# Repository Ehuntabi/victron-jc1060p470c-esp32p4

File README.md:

# Joint SPL 145 Control — VictronSolarDisplay port for Guition JC1060P470C_I (ESP32-P4)

**[Español](#español) | [English](#english)**

> La versión no se escribe aquí a mano (se queda vieja): se ve en el equipo en
> Ajustes → Acerca de, o con `git describe --tags --match "v*.*"`.

---

## Índice de documentación / Documentation index

| Si quieres... / If you want to... | Lee / Read |
|---|---|
| Instalar el firmware sin usar terminal / Install without a terminal | [`docs/INSTALACION.md`](docs/INSTALACION.md) |
| Desarrollar: mapa del código, comandos, hardware / Develop: code map, commands, hardware | [`CLAUDE.md`](CLAUDE.md) |
| Flujo multi-PC (sobremesa ↔ portátil) / Multi-PC dev workflow | [`docs/DESARROLLO.md`](docs/DESARROLLO.md) |
| Referencia de hardware: pinouts, esquemáticos, protocolo NE185 / Hardware reference | [`docs/`](docs/) |
| Historial de cambios por versión / Version changelog | [Releases de GitHub](https://github.com/Ehuntabi/victron-jc1060p470c-esp32p4/releases) |
| Guía operativa para la autocaravana (uso interno, portátil) / Motorhome operations guide (internal) | [`AUTOCARAVANA-SETUP.md`](AUTOCARAVANA-SETUP.md) |

---

## Capturas / Screenshots

<table>
  <tr>
    <td align="center"><br><sub>Vista general / Overview</sub></td>
    <td align="center"><br><sub>Batería / Battery</sub></td>
    <td align="center"><br><sub>Solar</sub></td>
  </tr>
  <tr>
    <td align="center"><br><sub>DC/DC</sub></td>
    <td align="center"><br><sub>Inversor / Inverter</sub></td>
    <td align="center"><br><sub>Monitor de batería / Battery monitor</sub></td>
  </tr>
  <tr>
    <td align="center"><br><sub>Frigo / Fridge</sub></td>
    <td align="center"><br><sub>Autocaravana / Motorhome</sub></td>
    <td align="center"><br><sub>Ajustes / Settings</sub></td>
  </tr>
</table>

---

## Español

Port del proyecto [victronsolardisplayesp (multi-device)](https://github.com/CamdenSutherland/victronsolardisplayesp/tree/multi-device) de CamdenSutherland, que a su vez es un fork de [VictronSolarDisplayEsp](https://github.com/wytr/VictronSolarDisplayEsp) de wytr.

Port realizado por **[Ehuntabi](https://github.com/Ehuntabi)**.

### Hardware

| Componente | Detalle |
|---|---|
| **Pantalla** | Guition JC1060P470C_I (7", 1024x600, DSI, touch GT911) |
| **SoC principal** | ESP32-P4 (RISC-V dual core 400 MHz, 32 MB PSRAM, 16 MB Flash) |
| **SoC WiFi/BT** | ESP32-C6 (SDIO vía esp_hosted: CLK=18, CMD=19, D0..D3=14..17) |
| **RTC** | RX8025T (I²C 0x32, SDA=7 / SCL=8 compartido con GT911 y ES8311) + pila CR1220 |
| **microSD** | **SDMMC** (slot 0 IOMUX: CLK=43, CMD=44, D0..D3=39..42; LDO interno canal 4 a 3,3 V), ver `components/datalogger/datalogger.c:241` |
| **Sensores temperatura** | DS18B20 1-Wire en **GPIO 4** (JP1 pin 13, pullup 4.7 kΩ) |
| **Ventilador frigo** | PWM LEDC en **GPIO 5** (JP1 pin 15), 18 kHz. El pin 15 ataca, a través de un optoacoplador **PC817**, un MOSFET **IRLR7843** con resistencia en serie en puerta, resistencia de pull-down y diodo **1N4148** de rueda libre |
| **Audio** | Codec ES8311 + amplificador NS4150 (PA_CTRL=11, I²S MCLK=13/BCLK=12/LRCK=10/DOUT=9) |
| **Cámara** | OmniVision **OV02C10** (MIPI-CSI 2 lanes, RAW10 1928x1092, ~37 fps, JPEG por HW). Comparte el I²C (SDA=7 / SCL=8); sin pines reset/pwdn dedicados |
| **NE185 (autocaravana)** | RS-485 con el cuadro Nordelettronica NE185 vía MAX485 (U8), **UART1 TX=GPIO 26 / RX=GPIO 27**, 38400 8N1, conector J4 (DE/RE automático) |
| **GPS** | u-blox **NEO-M9N** por **UART2 RX=GPIO 3 / TX=GPIO 2** (conector JP1), 38400 8N1. Solo se escucha NMEA; pone el reloj en hora solo |

> Pinout detallado con diagrama del JP1 (pines color-coded) y del CN2 en [`docs/pinout_guition_jc1060p470c_i.pdf`](docs/pinout_guition_jc1060p470c_i.pdf).

### Funcionalidades

#### UI estilo Venus OS
- Cards oscuras con borde de color por rol (cyan/verde/naranja/rojo/púrpura), métricas con número grande + unidad pequeña, pills de estado, gauges circulares para SOC y sombras suaves.
- **Iconos PNG propios** en headers de cards (batería de coche, panel solar, conversor DC/DC, casa) generados como `lv_img_dsc_t` embebidos en flash.
- Helpers reutilizables (`main/ui/ui_card.h`): `ui_card_create`, `ui_card_set_title_img`, `ui_metric_create_compact/_large`, `ui_pill_create`, `ui_arc_soc_create`, `ui_card_pulse`, paleta semántica `UI_COLOR_*`.
- **Pulso de actividad** en la card al recibir un BLE record (sombra anima 50→100→50 % en 600 ms, sin acumular animaciones).
- Pestañas Live/Settings ocultas — navegación con icono ⚙/🏠 discreto en la barra inferior + swipe horizontal del tabview. El botón Home **cierra la subpágina** y deja Settings en su menú principal.
- **Auto-vuelta a Live** tras 60 s sin actividad táctil.

#### Pantalla de bienvenida (splash)
- Logo de la furgo recortado con IA (rembg/u2net) y embebido a 720x400 RGB565 en flash.
- Animación de barra de progreso mientras dura la inicialización (BLE, audio, SD, BT).
- Configurable en Settings → Display: **Logo furgo** (default) o **Sin splash**.

#### Vistas Live
- **Overview** (default): fila horizontal Solar — Bat — Cargas con arc SOC central; debajo TTG + “PV X.X kWh · Cargas Y.Y kWh” acumulados del día.
- **Battery Monitor**: card naranja con arc SOC grande, V/A/W + pill enriquecido (“Cargando 5.5 A” / “Descargando 3.2 A”), barra bipolar de corriente ±50 A, sparkline de potencia (90 puntos), TTG / Consumido / Aux. Tap abre el histórico.
- **Solar Charger**: 2 cards (Solar verde + Salida batería naranja) con pill de estado (Bulk/Absorción/Float).
- **Default Battery**: 3 cards en fila (DC/DC cyan, Batería naranja con arc + sparkline + bar bipolar, Solar verde). En la card DC/DC el rótulo cambia entre `⚡ Alternador` (verde) o `🔋 Bat. motor` (gris) según la tensión.
- **Simple devices** (Inverter, Smart Lithium, AC Charger, etc.): card único con métricas apiladas; color e icono según tipo.
- **Pill rojo “FALLO: X”** en la card cuando un dispositivo Victron reporta `alarm_reason` (BMV/Inverter) o `charger_error` (Solar/DCDC/Orion).

#### Settings
Páginas con cards de borde de color, dropdown scrollable cuando hay overflow, separadores entre sub-bloques:
- **Historial en gráficos** (púrpura): chart 24 h de batería y de temperaturas frigo. Swipe izquierda/derecha **navega por fecha** en los logs guardados en SD (header muestra la fecha seleccionada).
- **Wi-Fi** (naranja): SSID, contraseña y switch on/off que se aplica **en caliente**, sin reiniciar la placa. (Cambiar SSID o contraseña sí necesita apagar y encender el switch para que entre.) Ojo: con el AP apagado, la pantalla de la cabina se queda sin telemetría.
- **Pantalla** (cyan): card combinada **Brillo pantalla + Salvapantallas**; card **Modo nocturno** en una línea (switch + Inicio/Fin + brillo nocturno, brillo aplicado automáticamente entre las horas configuradas según RTC); **Pantalla de bienvenida** (logo furgo o sin splash).
- **Tarjeta SD** (azul): carrusel de capturas y visor de imágenes de la SD.
- **Sonido y alertas** (rojo): volumen, switch silenciar avisos, umbrales SoC y temperatura del frigorífico.
- **Autocaravana** (rosa): agrupa lo propio del vehículo — **Opciones Frigo** (sensores DS18B20, control PWM del ventilador según T_Aletas, umbrales y aprovechamiento de excedente solar), **Victron Keys** (MAC + clave AES por dispositivo, hasta 8), **Modo ausente**, **Energía del viaje** (kWh/Ah cargados/consumidos y horas del viaje en curso), **Bombonas** (botón de *cambio de bombona* y estadística de cuánto dura cada una) y **Auto-encendido** de luz interior + bomba al arrancar.
- **Acerca de** (gris): uptime, RAM libre, IP del AP, chip, versión IDF, **Backup configuración** (exportar/importar a `/sdcard/config_backup.json`), **Último reset** + contador de resets por watchdog/panic, botón Reboot con confirmación.

#### Barra inferior
- Reloj + fecha (RTC), iconos interactivos:
  - 🔵 BLE — gris si no hay datos en 5 s.
  - 🔊 / 🔇 Volumen — tap = mute/unmute.
  - 📶 Wi-Fi — tap = toggle AP on/off en caliente. Verde: portal web accesible. Azul: AP encendido pero portal dormido por el auto-off. Gris: Wi-Fi deshabilitado.
  - ⚙ / 🏠 — navega entre Live y Settings.
  - 🌡 **Exterior: +26.0 °C** — temperatura del DS18B20 exterior, siempre visible a la derecha.

#### BLE Victron
- Hasta 8 dispositivos por MAC + clave AES (NVS).
- Records soportados: 0x01 Solar Charger, 0x02 Battery Monitor, 0x03 Inverter, 0x04 DC/DC Converter, 0x05 Smart Lithium, 0x09 SBP, 0x0A Lynx Smart BMS, 0x0B Multi RS, 0x0C VE.Bus, 0x0D DC Energy Meter, 0x0F Orion XS.
- Detección automática del tipo y vista correspondiente.

#### Cámara y modo vigilancia (autocaravana)
- Sensor **OmniVision OV02C10** por MIPI-CSI (2 lanes, RAW10 1928x1092, ~37 fps), driver propio portado del kernel Linux; **ISP por hardware** del ESP32-P4 (revelado del RAW con perfil IPA, no bypass) y **JPEG por hardware**. Comparte el bus I²C (SDA=7/SCL=8) con touch/RTC; sin pines dedicados.
- **Solo captura si alguien necesita la imagen**: vigilancia encendida, o el auto-brillo pidiendo la luz ambiente (`camera_set_luma_wanted`). En reposo no hace DQBUF, los buffers del driver se llenan y **el GDMA se para solo por contrapresión** — que es justo lo que deja libre la SD. Nunca streaming continuo.
  - Hasta el 24-ago-2026 cogía un fotograma **cada 2 s pasara lo que pasara**, para alimentar un auto-brillo que está DESACTIVADO en `main.c` desde hace tiempo: la cámara y su DMA trabajando 24 h al día, en un vehículo con baterías, para un dato que no leía nadie.
  - **La foto del portal no captura**: monta el JPEG con la última miniatura publicada. Por eso, con la cámara en reposo, `camera_snapshot_jpeg()` la despierta, espera un fotograma NUEVO (hasta 4 s) y, si no llega, **devuelve fallo en vez de servir una foto vieja**.
- `GET /snapshot`: última imagen en JPEG (recortada 960x528, calidad 78, ~80-150 KB).
- **Modo ausente / vigilancia**: se activa desde *Ajustes → Autocaravana* o con `GET /ausente?on` (cuenta atrás de 10 s y apaga la pantalla). Detección de movimiento por rejilla de luminancia 32x18; al detectar guarda una foto JPEG en **`/sdcard/vigilancia`**, así que **las fotos se conservan al reiniciar** (tope de 300 por sesión, anti-runaway). Galería en `GET /vigilancia` (y `/vigilancia/<id>` para cada foto); descarga completa en `GET /data/vigilancia.tar`. Se sale con **4 toques en cualquier esquina** (dentro de 3 s) o `GET /ausente?off`. *(Vídeo H.264: pendiente.)*
- **Cerrojo cámara↔SD** (`camera_sd_bus_lock`): cámara y SDMMC comparten GDMA; los escritores de SD (datalogger) serializan su E/S con este mutex para no provocar reinicios por INT_WDT.

#### NE185 — control de la autocaravana (RS-485)
- El P4 hace de **maestro RS-485** del cuadro de distribución **Nordelettronica NE185** (sustituye al panel NE187 retirado). MAX485 (U8) en **UART1** (TX=GPIO 26 / RX=GPIO 27, 38400 8N1), DE/RE automático por puerta NAND; conector J4 (A/B/GND/+5V).
- Polling cada 100 ms **alternando dos comandos "idle"** que imitan al NE187 (el NE185 solo devuelve datos si los ve alternados). Un botón = 8 tramas de pulsación (necesita ≥2) + 5 de reposo. Checksum + comprobación estructural; lectura robusta por barrido de fase (trama de 20 bytes y variante de 15 sin eco).
- Datos: **nivel de agua limpia** (0-4/4) y **grises** (lleno/vacío), luz interior/exterior, bomba, presencia de **230 V (shore)**, tensión de batería de **servicio** y de **motor**, y "fresco" (trama válida < 30 s).
- Controlable desde la UI (Overview) y por `POST /control`. Encendido automático de cargas al despertar (configurable, NVS).

#### Display satélite de cabina (UDP + HTTP)
- El satélite es la **3,5" de la cabina** (`~/joint/35cabina`).
- Broadcast **UDP** (1 Hz) desde el AP del 7" (`192.168.4.255:4242`). Payload compacto (**40 bytes, versión 5**, CRC32) con SoC/V/A de batería, canal auxiliar del shunt (batería motor), frigo (temperatura + ventilador), aguas del NE185, `epoch_local` (el reloj, que el satélite no tiene) y `gps_estado`. Protocolo compartido en `main/net/mini_proto.h`, **byte a byte idéntico** en los dos firmwares. Es "plan B" porque `esp_hosted` no exporta ESP-NOW.
- **Solo se manda lo FRESCO** (`bat_fresh`, `dcdc_fresh`, `cd.fresh`), no lo que hubo alguna vez: si el SmartShunt deja de hablar, a los 30 s se manda el centinela de "no hay dato" y el satélite lo enseña apagado. Mandar el último valor conocido sería un dato viejo con pinta de actual, que es peor que no tener dato.
- **La vuelta va por HTTP**, no por UDP: el satélite le manda a la P4 los apuntes del cuaderno con `POST /api/viaje` (ver abajo). Por TCP se sabe con certeza que han llegado.

#### Cuaderno de viaje (`POST /api/viaje`)
- La 3,5" de la cabina abre y cierra viajes y le manda los apuntes; la P4 es la dueña de los datos: crea `/sdcard/viajes/AAAA-MM-DD_Destino/`, escribe el diario, un **CSV por tipo** (`repostajes.csv`, `paradas.csv`, `pernoctas.csv`, `aguas.csv`, `itvs.csv`…) y, al cerrar, un `resumen.txt` en castellano llano.
- **Totales del viaje**: combustible y litros, peajes, gas, mantenimiento (con la ITV dentro), **aguas** y **alojamiento** (precio por noche × noches, más los servicios que se paguen aparte). Si aparece más de una moneda, el resumen **avisa** en vez de dar un total que parece bueno y no lo es.
- **El cuentakilómetros del cuadro, al salir y al llegar** (16-oct-2026): la cabina los pide al empezar y al cerrar el viaje (campo opcional `km_cuadro` del `inicio` y del `fin`; 0 = no apuntado) y el resumen escribe las dos lecturas y su diferencia frente al recorrido del GPS. Es el número que dice lo que ha hecho el viaje **de verdad**: si el GPS midió menos, se perdió un tramo (un túnel, un parking cubierto), y si al llegar marcan menos que al salir el resumen lo dice en vez de restar. Los dos viven en la NVS del viaje y se borran con sus totales.
- Los apuntes **sin viaje** (una salida puntual: repostar, ITV, taller) van al historial del vehículo en `/sdcard/vehiculo`, no a un viaje.
- **Cuenta los apuntes aplicados** y los compara con los que dice el satélite haber generado: si falta alguno, el viaje se marca **INCOMPLETO** al descargarlo, en vez de dárte­lo por bueno.
- La telemetría del viaje (cada 5 min) escribe **solo lecturas frescas**: con el SmartShunt apagado deja el hueco vacío en vez de repetir el último porcentaje hora tras hora. Un hueco se entiende; una lectura inventada se cree.
- Un apunte que no quepa se **rechaza entero con 413** y se dice por el log. Antes se recortaba en silencio: el JSON quedaba a medias, no parseaba, se devolvía *400 json inválido* y el satélite lo descartaba por malo — un dato perdido disfrazado de dato inválido.

#### GPS (NEO-M9N)
- Solo escucha NMEA a 38400 (lo de fábrica en la serie M9; los M8 venían a 9600, y probar a 9600 y no ver nada es el despiste clásico). No se le manda nada por UBX.
- **Pone el reloj en hora solo**, y únicamente con trama válida (`A`): el módulo da una hora aproximada de su reloj interno antes de fijar, y usarla sería empeorar la que ya tiene el RTC.
- **Pantalla propia en Ajustes → GPS**, con los tres estados diciendo QUÉ HACER: rojo *"sin señal del módulo"* (con el recordatorio de que RX/TX van cruzados), ámbar *"buscando satélites"* con los que ve, verde *"posición fijada"* con latitud, longitud y altitud. Debajo, las **últimas tramas en crudo** para diagnosticar.
- **El icono de la barra se toca y lleva a esa página.** Un indicador que avisa de que algo va mal y no lleva a donde se mira obliga a buscarlo por los menús.
- Mientras no hay posición, el log cuenta cada 10 s cuántas tramas llegan, cuántos satélites se ven y una trama de muestra; si no llega **nada**, recuerda que los cables van cruzados, que la alimentación es de 3,3 V y que son 38400 baudios. Se calla solo en cuanto fija.

#### Datalogger y persistencia
- **Frigo**: buffer circular RAM 200 entradas + CSV diario en `/sdcard/frigo/YYYY-MM-DD.csv`.
- **Batería**: 24 h en PSRAM (~945 KB) con muestreo cada 10 s y `avg/max/min` por intervalo. CSV diario en `/sdcard/bateria/YYYY-MM-DD.csv` (7 columnas).
- **kWh acumulados del día** (`/main/energy_today.c`): integra V·I·Δt desde BMV; prefiere `yield_today_centikwh` del SmartSolar para PV. Reset automático a medianoche. Persistencia NVS cada 5 min.
- **Bombonas** (`main/data/bombonas.c`): apunta la fecha/hora de cada **cambio** de bombona y saca la duración de cada una (la actual, la media y las últimas). Ojo con la distinción, que es el motivo de que exista: **comprarla** ya lo apunta el cuaderno de la cabina como gasto, pero comprar y usar son momentos distintos —una bombona puede pasarse meses de repuesto en el hueco—, así que lo que mide la duración es el cambio. Historial de 12 cambios en NVS y copia en `/sdcard/vehiculo/bombonas.csv`. Botón *Deshacer* para el dedazo, y si el reloj no está en hora **no apunta nada** en vez de inventar una fecha.
- **Energía del viaje** (`main/data/trip_computer.c`): kWh y Ah cargados/consumidos, horas activas, aporte solar y **kilómetros recorridos** (odómetro por GPS, muestreo cada 5 s; descarta saltos por debajo de 15 m —deriva estando parado— y por encima de 1 km, y al recuperar el fix se re-ancla en vez de contar la línea recta: peca por defecto antes que inventar). El recorrido se ve en Ajustes → GPS. Además, mientras hay viaje abierto se escribe un **`ruta.csv`** en su carpeta (posición cada 30 s, solo si el vehículo se ha movido ≥20 m: la decisión la toma el propio contador de km, para no tener dos criterios distintos de "se mueve"). Los puntos se acumulan en RAM y bajan a la tarjeta cada 5 min o cada 10 puntos, lo que llegue antes, siguiendo el mismo patrón que `datalogger` y `battery_history`: en FAT cada apertura reescribe FAT y directorio, y escribir punto a punto multiplicaba por diez el desgaste. En el cierre del viaje se vuelca lo pendiente. Persistencia NVS cada 5 min. Desde el 16-oct-2026 guarda además el **tiempo CONDUCIENDO** (suma de los intervalos del GPS —cada 5 s— con la velocidad del RMC por encima de 4 km/h; sin fix no cuenta, igual que el odómetro), que es lo que la pantalla de 5" enseña en su tarjeta del viaje y lo que sale como `Conduciendo:` en el resumen: no son las horas con el viaje abierto, porque las noches paradas de un viaje de tres días no son horas de volante. **Los pone a cero el inicio de viaje del cuaderno de la cabina** (`/api/viaje`), y el fin de viaje los cierra tras volcarlos al apartado ENERGIA del `resumen.txt` — así ese apartado es del viaje y no de una mezcla. En Ajustes queda un *Poner a cero* suelto para medir algo aparte. Hasta el 24-ago-2026 solo se reseteaban a mano y el resumen podía arrastrar la energía de viajes anteriores.
- Flush a SD periódico de frigo y batería; flush adicional antes de cualquier reset programado.
- Backup horario del epoch del sistema en NVS (`rtc_backup/epoch`).

#### Qué se borra solo de la tarjeta
- **Logs diarios a 120 días** (`log_cleanup.c`; las fotos de vigilancia siguen a 60): `/sdcard/frigo`, `/sdcard/bateria` y `/sdcard/ne185v` (este último escribe una línea por minuto y no lo limpiaba nadie hasta el 24-ago-2026). Solo borra ficheros con el nombre exacto `AAAA-MM-DD.csv`, y **nunca hoy ni ayer** aunque se le pida menos retención, para no chocar con una escritura en curso. Si el reloj no tiene fecha fiable, **aborta** en vez de borrar a ciegas.
- **Fotos de vigilancia a 60 días**: son carpetas de sesión `/sdcard/vigilancia/AAAAMMDD_HHMMSS/` con hasta 300 JPEG dentro — unos 60-120 KB cada uno, o sea **hasta ~35 MB por sesión**. El tope de 300 es POR SESIÓN y las sesiones no tienen límite: nada las borraba, y al llenarse la tarjeta se lleva por delante el cuaderno de viaje. Retención elegida por el usuario; son pruebas de un allanamiento y por eso 60 días y no menos.
- **NO se toca nunca**: `/sdcard/viajes`, `/sdcard/vehiculo` ni `/sdcard/config_backup`. Eso es justo lo que hay que conservar.

#### RTC y hora
- Zona horaria Europe/Madrid por defecto (CET/CEST), aplicada desde NVS al arrancar y preservada en el backup de configuración.
- El RTC almacena hora local; `mktime` la interpreta con la TZ activa.

#### Salvapantallas
- Modos **Atenuar** o **Rotar vistas** (Live → LogFrigo → LogBateria cada N min).
- Periodo y brillo de reposo configurables en Settings → Display.

#### Watchdog + auto-recovery
- Hardware (IDF): TWDT 10 s + INT_WDT 500 ms, ambos con panic + reset al disparar.
- Software (`/main/watchdog.c`): task monitor adicional que comprueba salud de LVGL cada 3 s; si el lock falla 3 veces consecutivas fuerza un reset controlado. También vigila por heartbeat las tareas de app (>10 s sin latido → reset). Grace period de 30 s al boot.
- **A propósito NO hace flush a SD antes de ese reset**: si el cuelgue lo causa el propio subsistema SD/FAT (mutex retenido por una tarea muerta), el flush haría deadlock y el reset nunca ocurriría. Se prefiere perder el último bloque de muestras a no reiniciar.
- **El motivo se traduce entero**: además de los de siempre, el P4 informa de USB (el reinicio de grabar por cable), JTAG, error de efuse, bajón de tensión y **bloqueo de CPU** (doble excepción). Hasta el 24-ago-2026 esos cinco salían como "Unknown" — el de bloqueo de CPU es un cuelgue de los gordos disfrazado de "no se sabe", y encima **no contaba** en el contador: la placa se reiniciaba sola sin dejar rastro.
- Contador de resets por TWDT/INT_WDT/panic/bloqueo de CPU **y por watchdog SW** en NVS, visible en Settings → About junto al motivo del último reinicio. Un reset forzado por el monitor SW aparece como `Watchdog SW (UI congelada)` o `Watchdog SW (tarea muda)`, no como un genérico "Software".
- **v1.4.4**: todo acceso a la SD se serializa con la cámara vía `camera_sd_bus_lock()` para evitar contención SDMMC → INT_WDT (recurrente en versiones previas). Los flushes periódicos de `datalogger`, `battery_history` y `ne185_vlog` tenían un `stat()` de comprobación de cabecera que se colaba FUERA de ese cerrojo — arreglado.
- **v1.5.2**: la actualización OTA se reiniciaba a medias con cualquier versión, por contención de caché entre núcleos durante la escritura de flash (`spi_flash_op_block_func` bloqueando al núcleo que no escribe; si se alarga por carga concurrente, el TWDT lo detecta como colgado). `CONFIG_SPIRAM_XIP_FROM_PSRAM` mueve la ejecución del firmware a PSRAM para que ese bloqueo no le quite el código a ningún núcleo, más el margen del TWDT subido a 10 s.

#### Portal web
- AP `VictronConfig` automático al arrancar.
- **Auto-off del servidor HTTP a los 15 min sin actividad** (peticiones, asociaciones o sondeos de un cliente; el AP **sigue emitiendo siempre**). No mira si queda alguien asociado: con un cliente callado, el portal se duerme igual (`AP_AUTO_OFF_MS` en `config_server_ap.c`).
  - Antes hacían falta **dos** clientes para mantenerlo vivo, porque el satélite viejo (el C6) estaba siempre asociado y solo *recibía* UDP. Con la 3,5" esa cuenta dejó de valer: ese satélite **habla por HTTP** para entregar los apuntes, y con el servidor apagado no podía. Como el auto-off solo se rearmaba con peticiones HTTP o con un cliente nuevo —y el satélite ya estaba asociado—, **la cola no se vaciaba nunca**: "N sin enviar" fijo en la cabina y `Connection reset by peer` al entregar, hasta reiniciar la P4 (24-ago-2026).
  - El ahorro se conserva: la 3,5" se apaga con el contacto, así que con el vehículo parado no queda nadie asociado y el portal se apaga igual.
  - Si el móvil ya estaba asociado y aun así no responde, hay un botón *Reactivar portal web* en Ajustes → Wi-Fi.
- **Seguridad — dos niveles** (`check_basic_auth` / `check_basic_auth_strict` en `config_server_auth.c`):
  - *Abierto — estado, cámara, descargas y los apuntes del satélite; hoy TAMBIÉN pide credenciales*: `PORTAL_REQUIRE_BASIC_AUTH` está a **1** desde el 21-ago-2026, así que este nivel exige el usuario y la clave **del portal** (los mismos que usan la app y las cabinas), **no** la clave de administración. Se cerró al comprobar que el AP **no tenía clave**: esp_hosted levantaba la red abierta con su nombre de fábrica, así que "estar en el Wi-Fi" era estar en la calle. Sigue cerrado aunque el AP ya vaya con WPA2 desde el 23-sep-2026 (ver la última viñeta): volver a abrirlo es una decisión aparte y hoy no está tomada.
  - *Estricto — `/ota`, `/save`, `/keys` y las capturas de `wifi`/`victron_keys`*: piden además la **clave de administración**. Son los que **reescriben el firmware**, **entregan las claves AES de los Victron** o **las enseñan en una captura**; sin esto, prestar el Wi-Fi a un invitado equivalía a darle control total. La app **sí usa `/ota`** (tiene un botón de actualizar firmware): con la clave de administración puesta, esa actualización desde el móvil da **401** y hay que hacerla desde el navegador, que es donde se teclea la clave; la app lo dice con un mensaje propio. El resto de la app (estado, control, cámara, descargas y apuntes) va por el nivel abierto. El navegador la pide una vez y la recuerda. Las dos claves se consultan en Ajustes → Wi-Fi.
  - Son dos claves distintas (portal vs. administración) a propósito: si el nivel abierto pidiera la de administración, generar esa clave dejaría fuera a las cabinas, que solo tienen la del portal (pasó hasta el 13-oct-2026 con `/api/viaje`; hoy va por el nivel abierto).
  - Sigue siendo HTTP plano sobre WPA2-PSK: protege del invitado al que le has dado el Wi-Fi, no de quien ya está dentro capturando tráfico.
  - Mitigaciones valoradas (08-sep-2026): el AP **usa WPA2-PSK con clave aleatoria** (`config_server_ap.c`, vía esp_hosted/C6) — **comprobado por el aire el 23-sep-2026**, despues de subir la radio (C6) y esp_hosted a 2.12.13: con el firmware viejo el AP salia ABIERTO y con otro nombre pese a configurarlo, que es lo que arreglo esa tanda. Ojo: host y esclavo van emparejados, ver `documentacion/C6_FIRMWARE_ACTUALIZACION.md`. Añadir TLS (`esp_https_server`) encima se descarta por ahora: exige certificado autofirmado (aviso de "conexión no privada" en cada navegador, mala primera impresión para lo que es un portal de configuración local), memoria extra por conexión TLS que compite con cámara/display/BLE, y protegería justo contra el escenario que ya se acepta como fuera de alcance (alguien que ya tiene la clave Wi-Fi). Si el umbral cambia (por ejemplo, si el AP dejara de requerir WPA2), reevaluar.
- Nav consistente en todas las páginas: **Dashboard · Logs · Keys**.
- `http://192.168.4.1/dashboard` (default): grid responsive con SoC, V/A/W, PV, DC/DC y energía de hoy. Auto-refresh 2 s via `GET /api/state` (JSON).
- `/data/frigo` y `/data/bateria`: gráficos SVG con auto-escala Y y downsample > 1500 puntos; polígono semitransparente max-min + línea avg.
- **Descargas sin sacar la SD**: `/data/frigo.csv` y `/data/bateria.csv` (día en curso), y los `.tar` completos de `/data/frigo.tar`, `/data/bateria.tar`, `/data/logs.tar`, `/data/config.tar`, `/data/capturas.tar` y `/data/vigilancia.tar`.
- **`/data/ne185v.csv` — log de diagnóstico NE185 vs SmartShunt** (día en curso, sin página ni gráfica). Una muestra por minuto en `/sdcard/ne185v/` con los **bytes 12/13 de la trama NE185 sin convertir** junto al voltaje que da el SmartShunt por BLE. Sirve para deducir por regresión la fórmula real del NE185: la documentada, `V = (raw − 30)/10`, viene del NE334 y **nunca se ha medido** aquí, porque el voltaje se lee del shunt y no de este bus. Columnas: `timestamp,ne_raw_serv,ne_raw_mot,ne_fresh,shunt_centivolts,shunt_fresh` (usar solo las filas con ambos `fresh = 1`).
- **Actualización por Wi-Fi (OTA)** en `http://192.168.4.1:8081/ota` (servidor pesado, puerto **8081**: `/ota` no está en el 80): se sube el `.bin` desde el navegador, sin cable ni PC.
- `/snapshot`: última foto de la cámara en JPEG. `/capturas` y `/captura?n=<0..23>`: capturas de las pantallas del propio display.
- `/keys`: configuración de claves Victron.
- Sincronización automática de hora (`` GET → `/settime`, compatible captive portal).

#### Backup/restore de configuración
- Exporta brightness, view_mode, zona horaria, modo nocturno, screensaver, alerts y flag debug. **OJO: las claves AES de los Victron NO se exportan a propósito** (el respaldo es un fichero de texto en la SD) a `/sdcard/config_backup.json` con cJSON.
- Importa desde el mismo fichero. La contraseña Wi-Fi **no** se exporta por seguridad.
- Botones Exportar/Importar en Settings → About.

### Compilación

Requisitos: **ESP-IDF v5.5.5 exactamente**, target esp32p4 (es la que usan el CI, `release.sh` y los `.bin` publicados).

```bash
git clone https://github.com/Ehuntabi/victron-jc1060p470c-esp32p4
cd victron-jc1060p470c-esp32p4
idf.py set-target esp32p4
idf.py build
scripts/grabar.sh /dev/ttyACM0   # graba lo PUBLICADO (y comprueba que lo esta)
```

### Configuración inicial

1. Encender la pantalla — el AP Wi-Fi `VictronConfig` arranca automáticamente.
2. Conectarse al AP desde móvil o PC y abrir `http://192.168.4.1` — por defecto se carga el **Dashboard**.
3. Navegar a **Keys** (link superior) e introducir la MAC y clave AES de cada dispositivo Victron.
4. Volver al Dashboard para ver los datos en vivo.

### Estado del hardware

- **SD Card** ✅ — slot 0 IOMUX dedicado.
- **RTC RX8025T** ✅ — soporta pérdida de pila con backup en NVS.
- **Cámara OV02C10** ✅ — MIPI-CSI con ISP por hardware. Comparte GDMA con la SD: captura a demanda, nunca streaming continuo.
- **NE185 (RS-485)** ✅ — MAX485 en UART1, en uso como maestro del cuadro.
- **GPS NEO-M9N** ⏳ — código listo y grabado (23-ago-2026), **módulo por conectar**:
  RX al GPIO 3, TX al GPIO 2, 3,3 V y GND, todo en el JP1. En cuanto hable, la
  pantalla se pone en hora sola. Indicador en la barra inferior y página propia
  en Ajustes → GPS con las tramas en crudo.
- **DS18B20** ✅ — bus 1-Wire en GPIO 4 (JP1 pin 13). Pullup 4.7 kΩ a 3.3 V externo. El bus necesita resets de warm-up antes de enumerar.
- **Ventilador** — PWM 18 kHz en GPIO 5 (JP1 pin 15).

### Créditos

- Proyecto original: VictronSolarDisplayEsp por wytr.
- Fork multi-device: victronsolardisplayesp por CamdenSutherland.
- Port ESP32-P4 / Guition JC1060P470C_I + UI estilo Venus OS + extensiones: Ehuntabi.

---

## English

Port of [victronsolardisplayesp (multi-device)](https://github.com/CamdenSutherland/victronsolardisplayesp/tree/multi-device) by CamdenSutherland, itself a fork of [VictronSolarDisplayEsp](https://github.com/wytr/VictronSolarDisplayEsp) by wytr.

Ported by **[Ehuntabi](https://github.com/Ehuntabi)**.

### Hardware

| Component | Details |
|---|---|
| **Display** | Guition JC1060P470C_I (7", 1024x600, DSI, GT911 touch) |
| **Main SoC** | ESP32-P4 (RISC-V dual core 400 MHz, 32 MB PSRAM, 16 MB flash) |
| **WiFi/BT SoC** | ESP32-C6 (SDIO via esp_hosted: CLK=18, CMD=19, D0..D3=14..17) |
| **RTC** | RX8025T (I²C 0x32, SDA=7 / SCL=8 shared with GT911 and ES8311) + CR1220 cell |
| **microSD** | SDMMC slot 0 IOMUX (CLK=43, CMD=44, D0..D3=39..42), internal LDO ch 4 (3.3 V) |
| **Temp sensors** | DS18B20 1-Wire on **GPIO 4** (JP1 pin 13, 4.7 kΩ pull-up) |
| **Fridge fan** | LEDC PWM on **GPIO 5** (JP1 pin 15), 18 kHz. Pin 15 drives, through a **PC817** optocoupler, an **IRLR7843** MOSFET with a series gate resistor, a pull-down resistor and a **1N4148** flyback diode |
| **Audio** | ES8311 codec + NS4150 amp (PA_CTRL=11, I²S MCLK=13/BCLK=12/LRCK=10/DOUT=9) |
| **Camera** | OmniVision **OV02C10** (MIPI-CSI 2 lanes, RAW10 1928x1092, ~37 fps, HW JPEG). Shares I²C (SDA=7 / SCL=8); no dedicated reset/pwdn pins |
| **NE185 (camper)** | RS-485 to the Nordelettronica NE185 panel via MAX485 (U8), **UART1 TX=GPIO 26 / RX=GPIO 27**, 38400 8N1, J4 connector (automatic DE/RE) |
| **GPS** | u-blox **NEO-M9N** on **UART2 RX=GPIO 3 / TX=GPIO 2** (JP1 header), 38400 8N1. NMEA listen-only; sets the clock by itself |

> Detailed pinout with colour-coded JP1 and CN2 diagrams in [`docs/pinout_guition_jc1060p470c_i.pdf`](docs/pinout_guition_jc1060p470c_i.pdf).

### Features

#### Venus-OS-style UI
- Dark cards with role-coloured borders (cyan/green/orange/red/purple), big-number metrics, status pills, circular SOC gauges, soft shadows.
- **Custom PNG icons** in headers (car battery, solar panel, DC/DC, house) embedded as `lv_img_dsc_t`.
- Reusable helpers in `main/ui/ui_card.h`: `ui_card_create`, `ui_card_set_title_img`, `ui_metric_create_compact/_large`, `ui_pill_create`, `ui_arc_soc_create`, `ui_card_pulse`, palette `UI_COLOR_*`.
- **Activity pulse** on card shadow when a BLE record arrives (600 ms ease-in-out, no anim stacking).
- Live/Settings tabs hidden — navigation via ⚙/🏠 icon in the bottom bar + horizontal swipe. The Home button **closes any sub-page** and leaves Settings on its main menu.
- **Auto-return to Live** after 60 s of touch inactivity.

#### Splash screen
- Camper photo cut out with AI (rembg/u2net) and embedded at 720x400 RGB565 in flash.
- Animated progress bar during init (BLE, audio, SD, BT).
- Configurable in Settings → Display: **Camper logo** (default) or **No splash**.

#### Live views
- **Overview** (default): horizontal row Solar — Battery — Loads with central SOC arc; below: TTG + “PV X.X kWh · Loads Y.Y kWh” today's totals.
- **Battery Monitor**: orange card with big SOC arc, V/A/W + enriched pill (“Charging 5.5 A” / “Discharging 3.2 A”), bipolar current bar ±50 A, power sparkline (90 points), TTG / Consumed / Aux. Tap opens history.
- **Solar Charger**: 2 cards (green Solar + orange Battery output) with charger state pill (Bulk/Absorption/Float).
- **Default Battery**: 3 cards (cyan DC/DC, orange Battery with arc + sparkline + bipolar bar, green Solar). DC/DC label switches between `⚡ Alternator` (green) and `🔋 Engine bat.` (grey) by voltage.
- **Simple devices** (Inverter, Smart Lithium, AC Charger, etc.): single card with stacked metrics.
- **Red “FAULT: X” pill** when a Victron device reports `alarm_reason` (BMV/Inverter) or `charger_error` (Solar/DCDC/Orion).

#### Settings
Pages with role-coloured cards, scrollbar visible on overflow, separators between sub-blocks:
- **Chart history** (purple): 24 h battery + frigo temperature charts. Swipe left/right **navigates by date** across SD logs (header shows the active day).
- **Wi-Fi** (orange): SSID, password and an on/off switch applied **live**, with no board restart. (Changing SSID or password does need the switch toggled off and on to take effect.) Note: with the AP off, the cabin display gets no telemetry.
- **Display** (cyan): combined **Brightness + Screensaver** card; single-line **Night mode** card (switch + start/end + night brightness, auto-applied within the time window by RTC); **Splash screen** (camper logo or none).
- **SD card** (blue): screenshot carousel and SD image viewer.
- **Sound & alerts** (red): volume, mute switch, SoC and freezer temperature thresholds.
- **Motorhome** (pink): groups everything vehicle-specific — **Fridge options** (DS18B20 sensors, PWM fan based on T_Fins, thresholds and solar-surplus usage), **Victron Keys** (MAC + AES key per device, up to 8), **Away mode**, **Energía del viaje** (kWh/Ah charged/discharged and hours for the current trip), **Bombonas** (gas-bottle *change* button plus how long each one lasts) and **Auto switch-on** of the interior light + pump at wake.
- **About** (gray): uptime, free RAM, AP IP, chip, IDF version, **Configuration backup** (export/import to `/sdcard/config_backup.json`), **Last reset** + WDT/panic reset counter, Reboot button.

#### Bottom bar
- Clock + date (RTC), interactive icons:
  - 🔵 BLE — grey if no data for 5 s.
  - 🔊 / 🔇 Volume — tap to mute/unmute.
  - 📶 Wi-Fi — tap to toggle the AP live. Green: web portal reachable. Blue: AP up but portal asleep after auto-off. Grey: Wi-Fi disabled.
  - ⚙ / 🏠 — navigate between Live and Settings.
  - 🌡 **Exterior: +26.0 °C** — outdoor DS18B20 reading, always visible on the right.

#### Victron BLE
- Up to 8 devices by MAC + AES key (NVS).
- Records: 0x01 Solar Charger, 0x02 Battery Monitor, 0x03 Inverter, 0x04 DC/DC Converter, 0x05 Smart Lithium, 0x09 SBP, 0x0A Lynx Smart BMS, 0x0B Multi RS, 0x0C VE.Bus, 0x0D DC Energy Meter, 0x0F Orion XS.
- Automatic device-type detection and matching view.

#### Camera & surveillance mode (camper)
- **OmniVision OV02C10** sensor over MIPI-CSI (2 lanes, RAW10 1928x1092, ~37 fps), custom driver ported from the Linux kernel; **hardware ISP** on the ESP32-P4 (RAW development with an IPA profile, not bypassed) and **hardware JPEG**. Shares the I²C bus (SDA=7/SCL=8) with touch/RTC; no dedicated pins.
- **It only captures when someone needs the image**: surveillance on, or auto-brightness asking for the ambient light (`camera_set_luma_wanted`). While idle it doesn't DQBUF, the driver buffers fill and **the GDMA stops on its own through backpressure** — which is exactly what frees the SD. Never continuous streaming.
  - Until 2026-08-24 it grabbed a frame **every 2 s no matter what**, to feed an auto-brightness that has been DISABLED in `main.c` for a long time: the camera and its DMA working 24/7, in a battery-powered vehicle, for a value nobody read.
  - **The portal snapshot doesn't capture**: it encodes the last published thumbnail. So with the camera idle, `camera_snapshot_jpeg()` wakes it, waits for a NEW frame (up to 4 s) and, if none arrives, **fails instead of serving a stale photo**.
- `GET /snapshot`: latest image as JPEG (cropped 960x528, quality 78, ~80-150 KB).
- **Away / surveillance mode**: enabled from *Settings → Motorhome* or via `GET /ausente?on` (10 s countdown, then the screen turns off). Motion detection via a 32x18 luminance grid; on a hit it stores a JPEG under **`/sdcard/vigilancia`**, so **photos survive a reboot** (capped at 300 per session as a runaway guard). Gallery at `GET /vigilancia` (and `/vigilancia/<id>` per photo); full download at `GET /data/vigilancia.tar`. Exit with **4 taps in any corner** (within 3 s) or `GET /ausente?off`. *(H.264 video: pending.)*
- **Camera↔SD lock** (`camera_sd_bus_lock`): camera and SDMMC share GDMA; SD writers (datalogger) serialize their I/O with this mutex to avoid INT_WDT resets.

#### NE185 — camper control (RS-485)
- The P4 acts as **RS-485 master** of the **Nordelettronica NE185** distribution panel (replacing the removed NE187 panel). MAX485 (U8) on **UART1** (TX=GPIO 26 / RX=GPIO 27, 38400 8N1), automatic DE/RE via NAND gate; J4 connector (A/B/GND/+5V).
- Polling every 100 ms **alternating two "idle" commands** that mimic the NE187 (the NE185 only returns data when it sees them alternated). One button = 8 press frames (needs ≥2) + 5 idle frames. Checksum + structural check; robust reading via phase sweep (20-byte frame and a 15-byte echo-less variant).
- Data: **fresh water level** (0-4/4) and **grey water** (full/empty), interior/exterior light, pump, presence of **230 V (shore)**, **service** and **engine** battery voltage, and "fresh" (valid frame < 30 s).
- Controllable from the UI (Overview) and via `POST /control`. Automatic load switch-on on wake (configurable, NVS).

#### Cabin satellite display (UDP + HTTP)
- The satellite is the **3.5" cabin display** (`~/joint/35cabina`).
- **UDP** broadcast (1 Hz) from the 7" AP (`192.168.4.255:4242`). Compact payload (**40 bytes, version 5**, CRC32) with battery SoC/V/A, shunt aux channel (starter battery), fridge (temperature + fan), NE185 water levels, `epoch_local` (the clock the satellite doesn't have) and `gps_estado`. Shared protocol in `main/net/mini_proto.h`, **byte-for-byte identical** in both firmwares. It's "plan B" because `esp_hosted` doesn't export ESP-NOW.
- **Only FRESH data is sent** (`bat_fresh`, `dcdc_fresh`, `cd.fresh`), never "we had it once": if the SmartShunt goes quiet, after 30 s the no-data sentinel is sent and the satellite greys it out. Sending the last known value would be stale data wearing a current-data face, which is worse than no data at all.
- **The return path is HTTP**, not UDP: the satellite posts trip notes to the P4 with `POST /api/viaje` (see below). Over TCP you know for certain they arrived.
- **The vehicle's odometer, on departure and on arrival** (2026-10-16): the cabin asks for both when starting and closing the trip (optional `km_cuadro` field in `inicio` and `fin`; 0 = not recorded) and the summary prints both readings and their difference against the GPS distance. That is the number that says what the trip really did: if the GPS measured less, a stretch was lost (a tunnel, an underground car park), and if the arrival reading is lower than the departure one the summary says so instead of subtracting. Both live in the trip's NVS and are cleared with its totals.

#### Datalogger and persistence
- **Frigo**: 200-entry RAM ring + daily CSV at `/sdcard/frigo/YYYY-MM-DD.csv`.
- **Battery**: 24 h in PSRAM (~945 KB) sampled every 10 s with avg/max/min per bin. Daily CSV at `/sdcard/bateria/YYYY-MM-DD.csv` (7 columns).
- **Today’s kWh accumulator** (`main/energy_today.c`): integrates V·I·Δt from BMV; prefers `yield_today_centikwh` from SmartSolar for PV. Auto-reset at midnight. NVS persistence every 5 min.
- **Bombonas** (`main/data/bombonas.c`): records the date/time of every gas-bottle **change** and derives how long each lasts (current one, average, last few). The distinction is the point: **buying** a bottle is already logged as an expense by the cabin notebook, but buying and fitting are different moments —a spare can sit in the locker for months— so it is the change that measures duration. 12 changes kept in NVS plus a copy in `/sdcard/vehiculo/bombonas.csv`. An *Undo* button covers mis-taps, and if the clock is not set it records **nothing** rather than inventing a date.
- **Energía del viaje** (`main/data/trip_computer.c`): kWh and Ah charged/discharged, active hours, solar contribution and **distance travelled** (GPS odometer sampled every 5 s; discards jumps below 15 m —drift while parked— and above 1 km, and re-anchors after a lost fix instead of counting the straight line: it under-reports rather than invents). Distance is shown in Settings → GPS. While a trip is open a **`ruta.csv`** track is also written into its folder (a fix every 30 s, only when the vehicle has moved ≥20 m — the decision comes from the km counter itself, so there is a single definition of "moving"). Points are buffered in RAM and flushed every 5 min or every 10 points, whichever comes first — the same pattern as `datalogger` and `battery_history`: on FAT every open rewrites the FAT and the directory entry, so writing point by point multiplied wear tenfold. Pending points are flushed when the trip closes. NVS persistence every 5 min. Since 2026-10-16 it also keeps the **DRIVING time** (sum of the GPS intervals —every 5 s— with the RMC speed above 4 km/h; without a fix nothing is counted, same as the odometer), which is what the 5" screen shows in its trip card and what appears as `Conduciendo:` in the summary: not the hours with the trip open, because the parked nights of a three-day trip are not hours at the wheel. **Zeroed by the cabin notebook's trip start** (`/api/viaje`) and closed by the trip end, after they are written into the `resumen.txt` ENERGIA section — so that section belongs to that trip only. A standalone *Poner a cero* remains in Settings. Until 2026-08-24 they were reset by hand only, so a summary could carry energy from previous trips.
- Periodic SD flush of frigo and battery logs; extra flush before any scheduled reset.
- Hourly NVS backup of the system epoch (`rtc_backup/epoch`).

#### What gets deleted from the card automatically
- **Daily logs after 120 days** (`log_cleanup.c`; surveillance photos stay at 60): `/sdcard/frigo`, `/sdcard/bateria` and `/sdcard/ne185v` (the latter writes one line per minute and nothing cleaned it until 2026-08-24). Only files named exactly `YYYY-MM-DD.csv`, and **never today or yesterday** even if asked for a shorter retention, so it can't race an in-flight write. If the clock has no trustworthy date it **aborts** instead of deleting blindly.
- **Surveillance photos after 60 days**: session folders `/sdcard/vigilancia/YYYYMMDD_HHMMSS/` holding up to 300 JPEGs — 60-120 KB each, i.e. **up to ~35 MB per session**. The 300 cap is PER SESSION and sessions were unbounded: nothing ever deleted them, and a full card takes the trip notebook down with it.
- **Never touched**: `/sdcard/viajes`, `/sdcard/vehiculo` or `/sdcard/config_backup`. That's exactly what must be kept.

#### RTC and time
- Europe/Madrid timezone by default (CET/CEST), applied from NVS at boot and preserved in the configuration backup.
- RTC stores local time; `mktime` interprets it with the active TZ.

#### Screensaver
- Modes **Dim** or **Rotate views** (cycle Live → FrigoLog → BatteryLog every N min).
- Period and idle brightness configurable in Settings → Display.

#### Watchdog + auto-recovery
- Hardware (IDF): TWDT 10 s + INT_WDT 500 ms, both panic + reset.
- Software (`main/watchdog.c`): monitor task that checks LVGL health every 3 s; if the lock fails 3 times in a row it forces a controlled reset. It also watches app tasks by heartbeat (>10 s silent → reset). 30 s grace period at boot.
- **It deliberately does NOT flush to SD before that reset**: if the hang is caused by the SD/FAT subsystem itself (mutex held by a dead task), the flush would deadlock and the reset would never happen. Losing the last block of samples beats not rebooting.
- Reset counter for TWDT/INT_WDT/panic **and SW watchdog** in NVS, shown in Settings → About next to the last reset reason. A reset forced by the SW monitor reads as `Watchdog SW (UI congelada)` or `Watchdog SW (tarea muda)` rather than a generic "Software".
- **v1.4.4**: every SD access is serialized with the camera via `camera_sd_bus_lock()` to avoid SDMMC contention → INT_WDT (recurring in earlier versions). The periodic flushes in `datalogger`, `battery_history` and `ne185_vlog` had a header-check `stat()` that slipped OUTSIDE that lock — fixed.
- **v1.5.2**: Wi-Fi OTA updates kept restarting mid-upload on any version, due to cross-core cache contention during flash writes (`spi_flash_op_block_func` blocks the core not writing; if that stretches out under concurrent load, the TWDT sees it as hung). `CONFIG_SPIRAM_XIP_FROM_PSRAM` moves firmware execution to PSRAM so that block no longer starves either core of code to run, plus the TWDT margin raised to 10 s.

#### Web portal
- `VictronConfig` AP starts automatically on boot.
- **HTTP server auto-off after 15 min without activity** (requests, associations or client probes; the **AP itself never stops**). It does not check whether a client is still associated: an idle client does not keep it awake (`AP_AUTO_OFF_MS` in `config_server_ap.c`).
  - It used to require **two** clients to stay alive, because the old satellite (the C6) was always associated and only *received* UDP. That no longer holds with the 3.5": this satellite **speaks HTTP** to deliver trip notes, and with the server off it couldn't. Since auto-off was only re-armed by HTTP requests or by a *new* client — and the satellite was already associated — **the queue never drained**: a permanent "N sin enviar" in the cabin and `Connection reset by peer` on delivery, until the P4 was rebooted (2026-08-24).
  - Power saving is preserved: the 3.5" powers off with the ignition, so with the vehicle parked nobody is associated and the portal shuts down as before.
  - If the phone was already associated and it still doesn't answer, there is a *Reactivar portal web* button in Settings → Wi-Fi.
- **Security — two tiers** (`check_basic_auth` / `check_basic_auth_strict` in `config_server_auth.c`):
  - *Open — state, camera, downloads and the satellite's trip notes; today it ALSO requires credentials*: `PORTAL_REQUIRE_BASIC_AUTH` is **1** since 2026-08-21, so this tier asks for the **portal** user and password (the same ones the app and the cabins use), **not** the admin key. It was closed when we found the AP **had no key at all**: esp_hosted brought the network up open with its factory name, so "being on the Wi-Fi" meant being on the street. It stays closed even though the AP has used real WPA2 since 2026-09-23 (last bullet): reopening it is a separate decision and has not been made.
  - *Strict — `/ota`, `/save`, `/keys` and the `wifi`/`victron_keys` screenshots*: these also require the **admin key**. They **rewrite the firmware**, **hand over the Victron AES keys** or **show those keys in a screenshot**; without this, lending someone the Wi-Fi key amounted to giving them full control. The app **does use `/ota`** (it has a firmware-update button): with the admin key set, that update from the phone returns **401** and has to be done from the browser, where the key is typed; the app says so with its own message. The rest of the app (state, control, camera, downloads, trip notes) uses the open tier. A browser asks once and remembers. Both keys are shown in Settings → Wi-Fi.
  - The two tiers use different keys (portal vs. admin) on purpose: if the open tier required the admin key, generating that key would lock the cabins out, since they only hold the portal one (which is what happened with `/api/viaje` until 2026-10-13; it now uses the open tier).
  - It is still plain HTTP over WPA2-PSK: it protects against the guest you handed the Wi-Fi to, not against someone already inside capturing traffic.
  - Mitigations evaluated (2026-09-08): the AP **already uses WPA2-PSK with a random key** (`config_server_ap.c`, via esp_hosted/C6) — that part is already done, not an open item. Adding TLS (`esp_https_server`) on top is set aside for now: it needs a self-signed certificate (every browser shows a "connection not private" warning, a poor first impression for what is a local config portal), extra memory per TLS connection competing with camera/display/BLE, and it would only protect against the scenario already accepted as out of scope (someone who already has the Wi-Fi key). Revisit if that threshold changes (e.g. if the AP stopped requiring WPA2).
- Consistent navigation across pages: **Dashboard · Logs · Keys**.
- `http://192.168.4.1/dashboard` (default): responsive grid with SoC, V/A/W, PV, DC/DC and today's energy. Auto-refresh every 2 s via `GET /api/state` (JSON).
- `/data/frigo` and `/data/bateria`: SVG charts with Y-axis autoscale and downsample over 1500 points; semitransparent max-min envelope + average line.
- **Downloads without pulling the SD card**: `/data/frigo.csv` and `/data/bateria.csv` (current day), plus full archives at `/data/frigo.tar`, `/data/bateria.tar`, `/data/logs.tar`, `/data/config.tar`, `/data/capturas.tar` and `/data/vigilancia.tar`.
- **`/data/ne185v.csv` — NE185 vs SmartShunt diagnostic log** (current day; no page, no chart). One sample per minute under `/sdcard/ne185v/` holding the **raw, unconverted bytes 12/13 of the NE185 frame** next to the battery voltage reported by the SmartShunt over BLE. Its purpose is to derive the NE185's real formula by regression: the documented one, `V = (raw − 30)/10`, is inherited from the NE334 and **has never been measured** here, because voltage is read from the shunt rather than from this bus. Columns: `timestamp,ne_raw_serv,ne_raw_mot,ne_fresh,shunt_centivolts,shunt_fresh` (use only rows where both `fresh = 1`).
- **Wi-Fi firmware update (OTA)** at `http://192.168.4.1:8081/ota` (heavy server, port **8081**: `/ota` is not on port 80): upload the `.bin` from the browser — no cable, no PC.
- `/snapshot`: latest camera frame as JPEG. `/capturas` and `/captura?n=<0..23>`: screenshots of the display's own screens.
- `/keys`: Victron key configuration page.
- Automatic time sync via `` GET → `/settime` (captive-portal compatible).

#### Configuration backup/restore
- Exports brightness, view_mode, timezone, night mode, screensaver, alerts and debug flag. **NOTE: Victron AES keys are deliberately NOT exported** (the backup is plain text on the SD card) to `/sdcard/config_backup.json` via cJSON.
- Imports from the same file. The Wi-Fi password is **not** exported for safety.
- Export/Import buttons in Settings → About.

### Build

Requirements: **ESP-IDF v5.5.5 exactly**, target esp32p4 (the one used by CI, `release.sh` and the published `.bin`s).

```bash
git clone https://github.com/Ehuntabi/victron-jc1060p470c-esp32p4
cd victron-jc1060p470c-esp32p4
idf.py set-target esp32p4
idf.py build
scripts/grabar.sh /dev/ttyACM0   # graba lo PUBLICADO (y comprueba que lo esta)
```

### First-time setup

1. Power on the display — the `VictronConfig` Wi-Fi AP starts automatically.
2. Connect to the AP from your phone or PC and open `http://192.168.4.1` — the **Dashboard** loads by default.
3. Click **Keys** in the top nav and enter the MAC and AES key for each Victron device.
4. Back to Dashboard to see live data.

### Hardware status

- **SD card** ✅ — dedicated IOMUX slot 0.
- **RTC RX8025T** ✅ — survives battery loss with NVS backup.
- **OV02C10 camera** ✅ — MIPI-CSI with hardware ISP. Shares GDMA with the SD card: capture on demand, never continuous streaming.
- **NE185 (RS-485)** ✅ — MAX485 on UART1, in use as master of the distribution panel.
- **DS18B20** ✅ — 1-Wire bus on GPIO 4 (JP1 pin 13). External 4.7 kΩ pull-up to 3.3 V. The bus needs warm-up resets before enumerating.
- **Fan** — 18 kHz PWM on GPIO 5 (JP1 pin 15).

### Credits

- Original project: VictronSolarDisplayEsp by wytr.
- Multi-device fork: victronsolardisplayesp by CamdenSutherland.
- ESP32-P4 / Guition JC1060P470C_I port + Venus-OS-style UI + extensions: Ehuntabi.

This project keeps the same license as the original. See LICENSE.

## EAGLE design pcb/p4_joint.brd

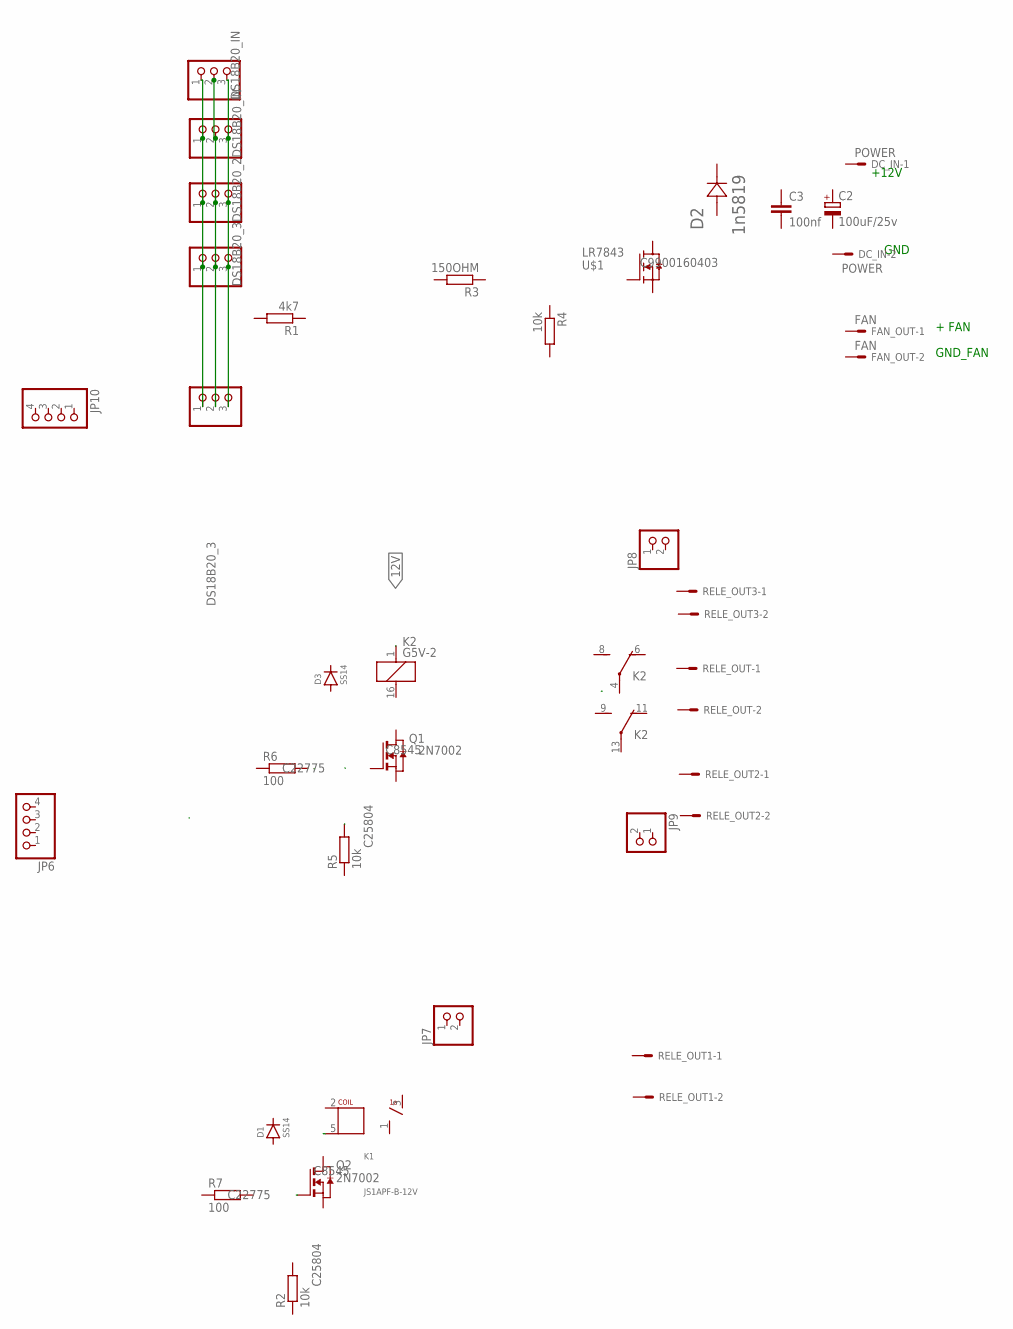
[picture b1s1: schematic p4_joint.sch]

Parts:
C2: 100uF/25v; PANASONIC_C
C3: 100nf; C0603
D1, D3: SS14; SMA
D2: 1n5819; SOD123-M
DC_IN: POWER; KK-156-2
FAN_OUT: FAN; KK-156-2
JP1, JP2: DS18B20_IN; 1X03
JP3, JP5: DS18B20_3; 1X03
JP4: DS18B20_2; 1X03
JP6, JP10: PINHD-1X4; 1X04
JP7, JP8, JP9: PINHD-1X2; 1X02
K1: JS1APF-B-12V; JS_RELAY_1A
K2: G5V-2
Q1, Q2: 2N7002; SOT-23; LCSC C8545
R1: 4k7; R0603
R2, R5: 10k; R0805; LCSC C25804
R3: 150OHM; R0603
R4: 10k; R0603
R6, R7: 100; R0805; LCSC C22775
RELE_OUT, RELE_OUT1, RELE_OUT2, RELE_OUT3: KK-156-2
U$1: LR7843; TO252; LCSC C9900160403

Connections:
12V: K2.1
unnamed: JP1.3, JP2.3, JP3.3, JP4.3, JP5.3
unnamed: JP1.2, JP2.2, JP3.2, JP4.2, JP5.2
unnamed: JP1.1, JP2.1, JP3.1, JP4.1, JP5.1

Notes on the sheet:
+12V
GND
GND_FAN
+ FAN

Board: 2 copper layers, 33 parts (0 on the bottom side), 3 nets, no tracks yet.

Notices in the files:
parts and their libraries:
COPYRIGHT: Copyright C 2015 Accelerated Designs. All rights reserved
